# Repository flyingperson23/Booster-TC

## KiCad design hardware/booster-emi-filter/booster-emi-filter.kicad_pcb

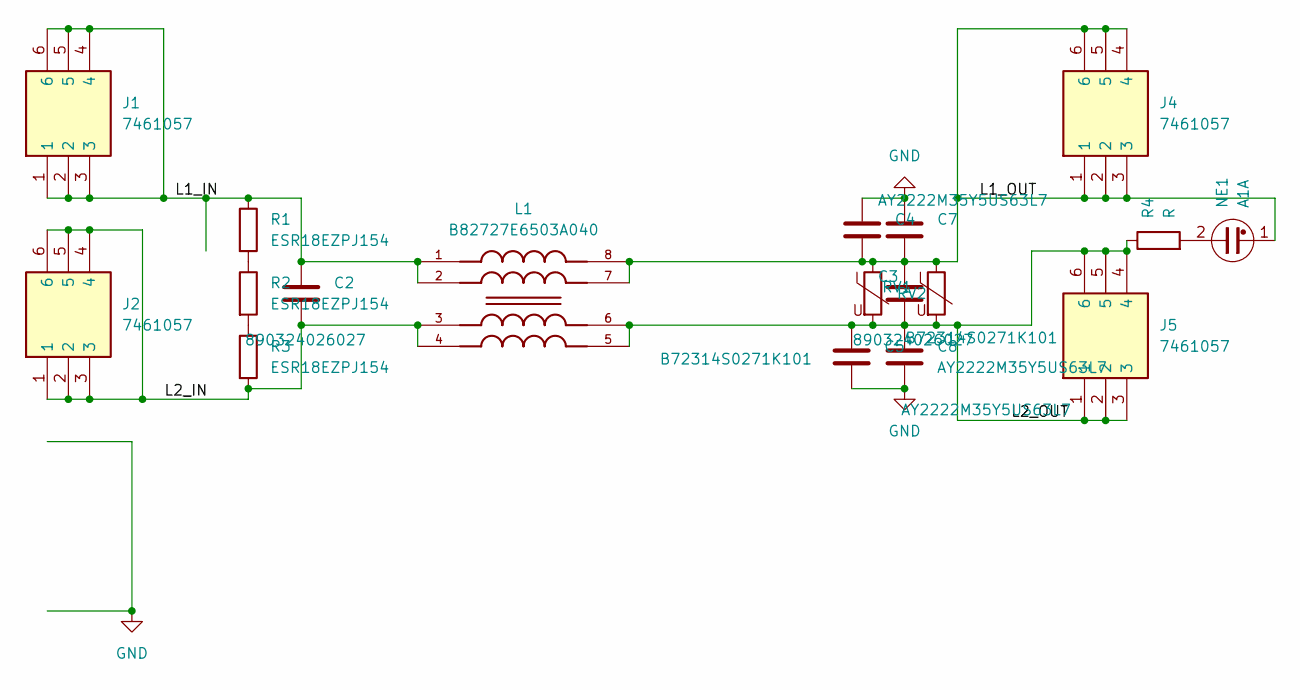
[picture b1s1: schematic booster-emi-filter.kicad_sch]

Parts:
C2, C3: 890324026027
C4, C5, C7, C8: AY2222M35Y5US63L7
J1, J2, J4, J5: 7461057; Mouser Part Number 710-7461057
L1: B82727E6503A040; IND_B82727E6503A040; PARTREV May 2015
NE1: A1A; NEON-A1A
R1, R2, R3: ESR18EZPJ154; R_1206_3216Metric_Pad1.30x1.75mm_HandSolder
R4: R; R_Axial_DIN0207_L6.3mm_D2.5mm_P7.62mm_Horizontal
RV1, RV2: B72314S0271K101

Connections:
/L1_IN: C2.1, J1.1, J1.2, J1.3, J1.4, J1.5, J1.6, L1.1, L1.2, R1.1
/L1_OUT: C3.1, C4.2, C7.2, J4.1, J4.2, J4.3, J4.4, J4.5, J4.6, L1.7, L1.8, NE1.1, RV1.1, RV2.1
/L2_IN: C2.2, J2.1, J2.2, J2.3, J2.4, J2.5, J2.6, L1.3, L1.4, R3.2
/L2_OUT: C3.2, C5.1, C8.1, J5.1, J5.2, J5.3, J5.4, J5.5, J5.6, L1.5, L1.6, R4.1, RV1.2, RV2.2
GND: C4.1, C5.2, C7.1, C8.2
unnamed: NE1.2, R4.2
unnamed: R1.2, R2.1
unnamed: R2.2, R3.1

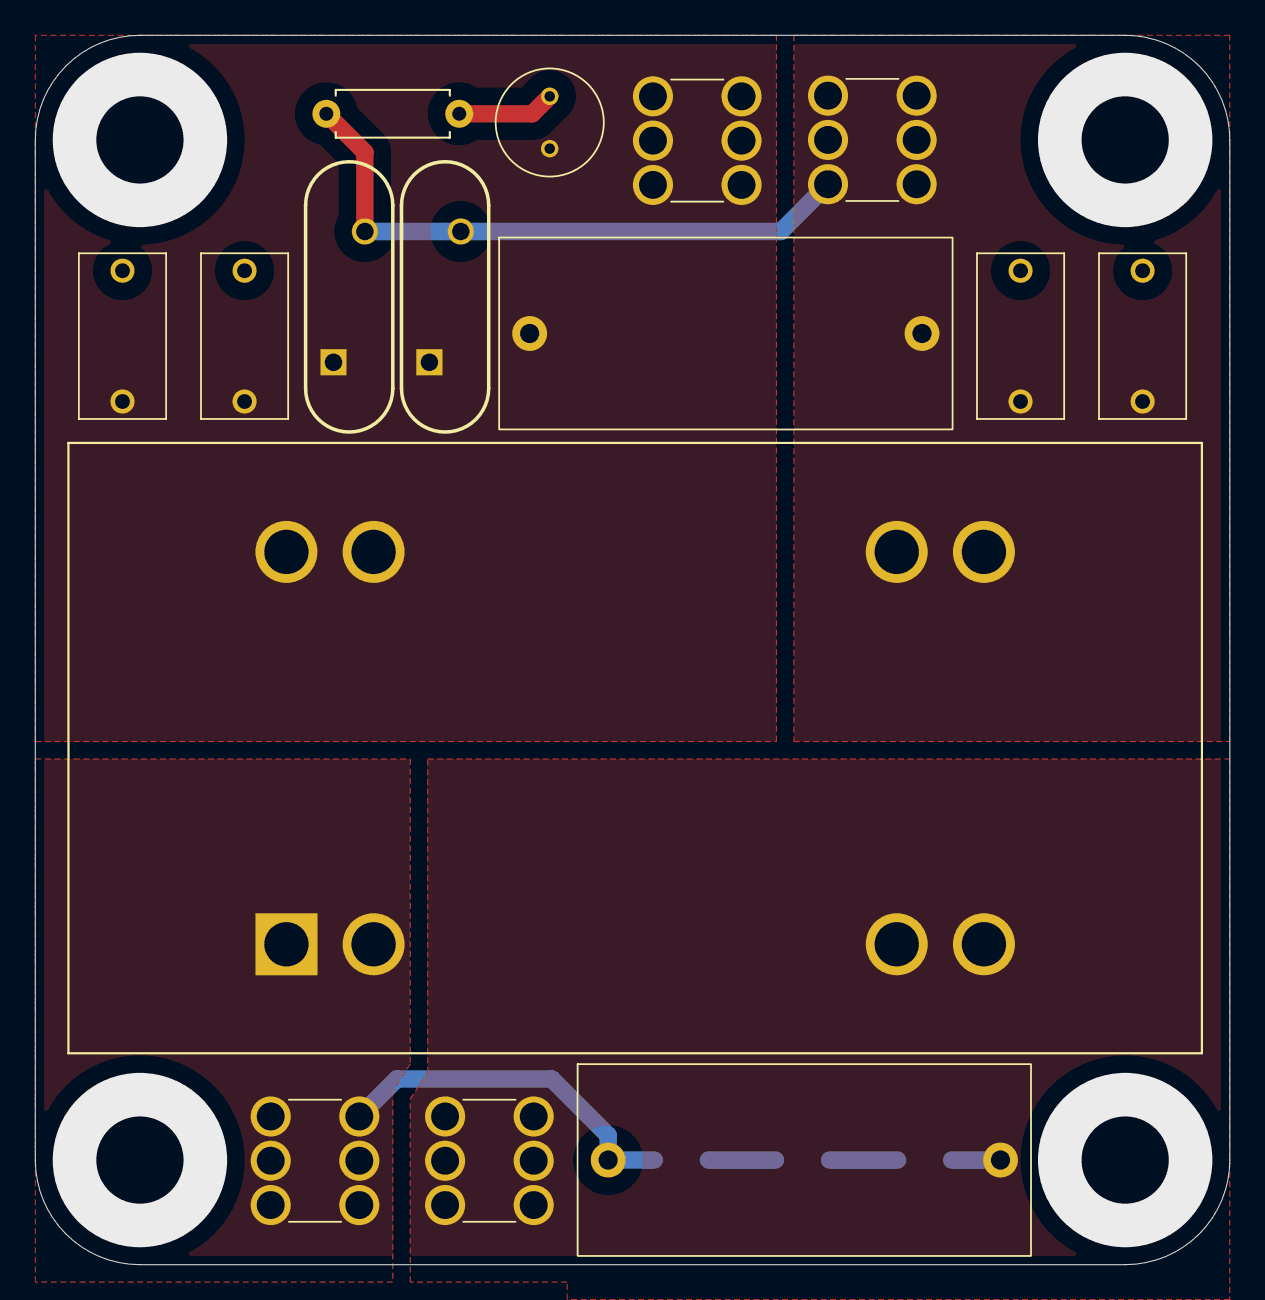
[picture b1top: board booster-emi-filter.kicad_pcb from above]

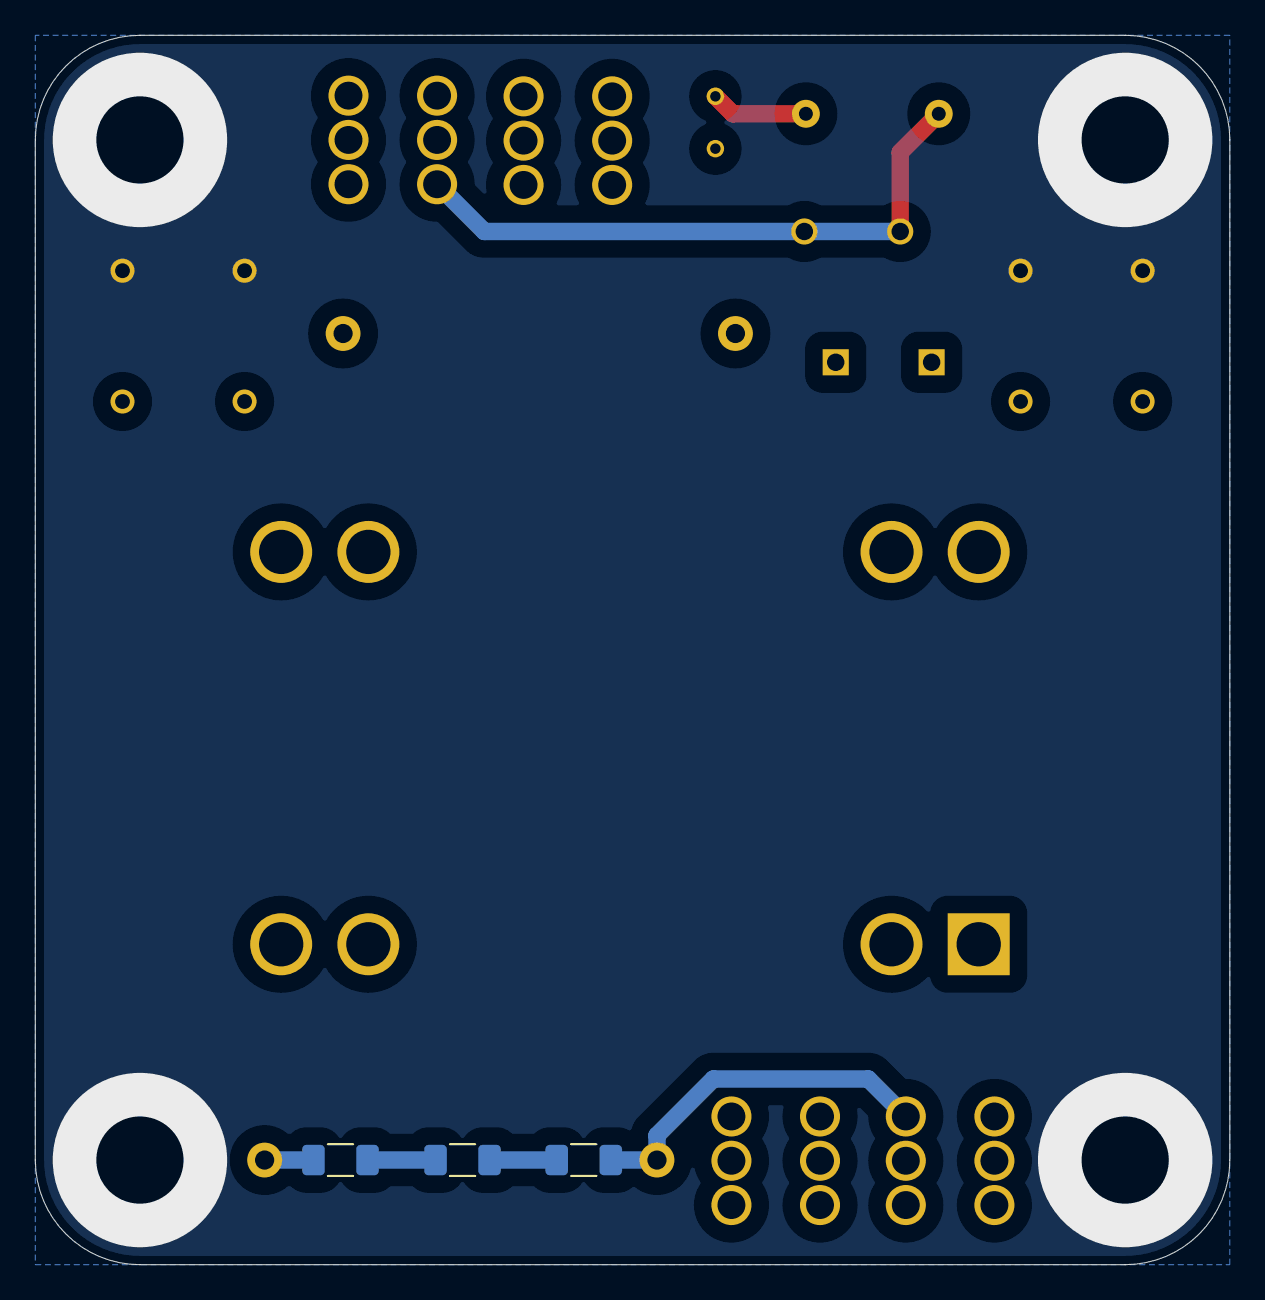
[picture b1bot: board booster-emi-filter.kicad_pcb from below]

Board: 2 copper layers, 68.5 x 70.5 mm, 18 parts (3 on the bottom side), 8 nets.

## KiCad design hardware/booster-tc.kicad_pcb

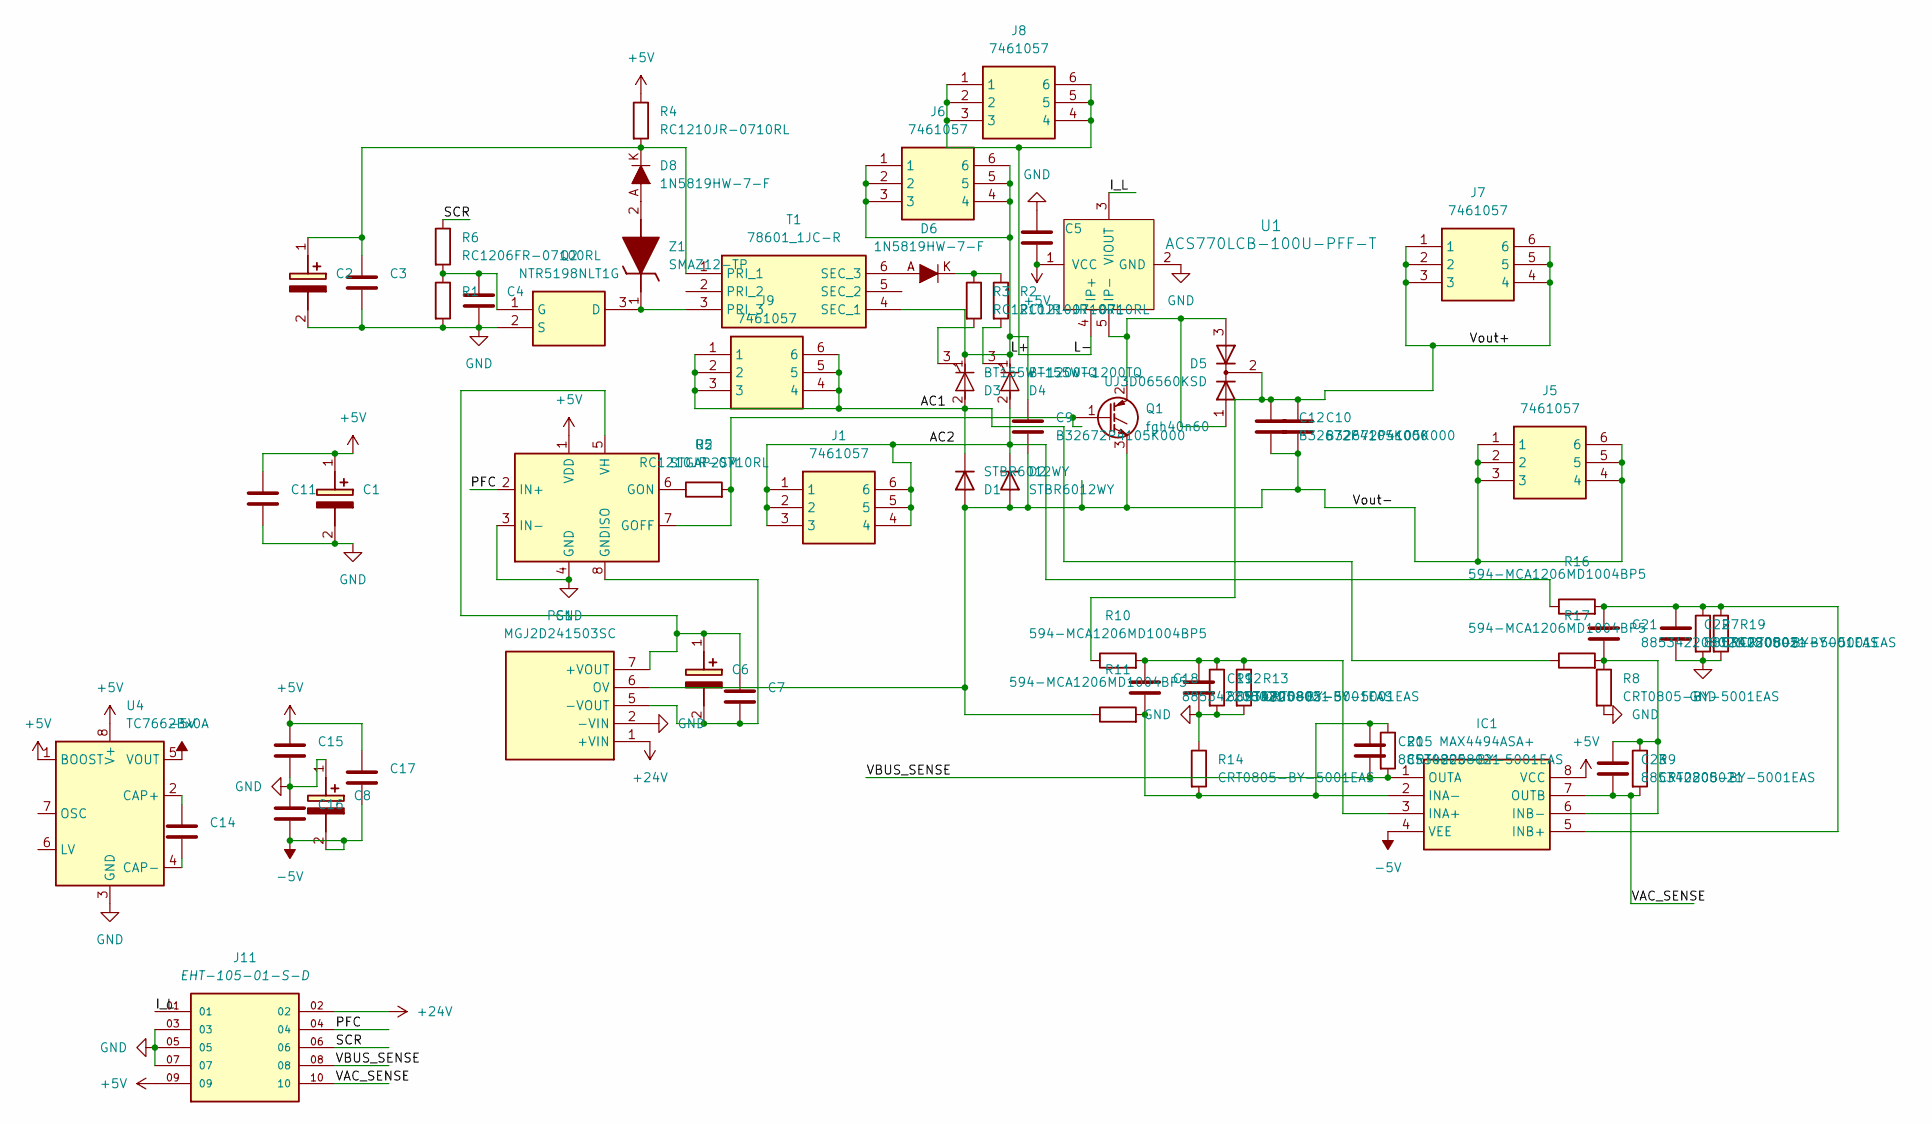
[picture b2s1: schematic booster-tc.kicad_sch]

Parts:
C1, C2, C6, C8: 860020474014; CAPPRD350W52D800H1300; Mouser Part Number 710-860020474014
C3, C5, C7: 885012210031; C_1812_4532Metric_Pad1.57x3.40mm_HandSolder
C4, C11, C14, C15, C16, C17: 885012208022; C_1206_3216Metric_Pad1.33x1.80mm_HandSolder
C9, C10, C12: B32672P4105K000
C18, C19, C20, C21, C22, C23: 885342208021; C_1206_3216Metric_Pad1.33x1.80mm_HandSolder
D1, D2: STBR6012WY; TO-247-2_Horizontal_TabDown
D3, D4: BT155W-1200TQ; TO-247-3_Horizontal_TabDown
D5: UJ3D06560KSD; TO-247-3_Horizontal_TabDown
D6, D8: 1N5819HW-7-F; SOD-123; MPN 1N5819HW-7-F
IC1: MAX4494ASA+; SOIC127P600X175-8N; Mouser Part Number 700-MAX4494ASA
J1, J5, J6, J7, J8, J9: 7461057; Mouser Part Number 710-7461057
J11: EHT-105-01-S-D; SAMTEC_EHT-105-01-S-D
PS1: MGJ2D241503SC; Mouser Part Number 580-MGJ2D241503SC
Q1: fgh40n60; TO-247-3_Horizontal_TabDown
Q2: NTR5198NLT1G; SOT96P237X111-3N; Mouser Part Number 863-NTR5198NLT1G
R1: RC1206FR-0710KL; R_1206_3216Metric
R2, R3, R4, R5: RC1210JR-0710RL; C_1210_3225Metric_Pad1.33x2.70mm_HandSolder
R6: RC1206FR-07100RL; R_1206_3216Metric_Pad1.30x1.75mm_HandSolder
R7, R8, R9, R12, R13, R14, R15, R19: CRT0805-BY-5001EAS; R_0805_2012Metric_Pad1.20x1.40mm_HandSolder
R10, R11, R16, R17: 594-MCA1206MD1004BP5; R_1206_3216Metric_Pad1.30x1.75mm_HandSolder
T1: 78601_1JC-R; SOP254P1270X665-6N; Mouser Part Number 580-78601/1JC-R
U1: ACS770LCB-100U-PFF-T; CB-5_Formed_Leads; MPN ACS770LCB-100U-PFF-T
U2: STGAP2SM; SOIC-8_3.9x4.9mm_P1.27mm
U4: TC7662Bx0A; SOIC-8_3.9x4.9mm_P1.27mm
Z1: SMAZ12-TP; DIOM5226X244N; Mouser Part Number 833-SMAZ12-TP

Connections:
+5V: C1.1 (+), C5.2, C11.1, C15.1, C17.1, IC1.8 (VCC), J11.09, R4.1, U1.1 (VCC), U2.1 (VDD), U4.1 (BOOST), U4.8 (V+)
+24V: J11.02, PS1.1 (+VIN)
-5V: C8.2 (-), C16.2, C17.2, IC1.4 (VEE), U4.5 (VOUT)
/AC1: D1.1 (K), D3.2 (A), J9.1, J9.2, J9.3, J9.4, J9.5, J9.6, R17.1
/AC2: D2.1 (K), D4.2 (A), J1.1, J1.2, J1.3, J1.4, J1.5, J1.6, R16.1
/I_L: J11.01, U1.3 (VIOUT)
/L+: C9.1, D3.1 (K), D4.1 (K), J6.1, J6.2, J6.3, J6.4, J6.5, J6.6, T1.4 (SEC_1)
/L-: J8.1, J8.2, J8.3, J8.4, J8.5, J8.6, U1.4 (IP+)
/PFC: J11.04, U2.2 (IN+)
/SCR: J11.06, R6.1
/VAC_SENSE: C23.2, IC1.7 (OUTB), J11.10, R9.2
/VBUS_SENSE: C20.2, IC1.1 (OUTA), J11.08, R15.2
/Vout+: C10.1, C12.1, D5.2 (K), J7.1, J7.2, J7.3, J7.4, J7.5, J7.6, R10.1
/Vout-: C9.2, C10.2, C12.2, D1.2 (A), D2.2 (A), J5.1, J5.2, J5.3, J5.4, J5.5, J5.6, PS1.6 (OV), Q1.3 (E), R11.1
GND: C1.2 (-), C2.2 (-), C3.2, C4.2, C5.1, C8.1 (+), C11.2, C15.2, C16.1, C19.2, C22.2, J11.03, J11.05, J11.07, PS1.2 (-VIN), Q2.2 (S), R1.2, R7.2, R8.2, R12.2, R13.2, R14.1, R19.2, U1.2 (GND), U2.3 (IN-), U2.4 (GND), U4.3 (GND)
unnamed: C2.1 (+), C3.1, D8.K, R4.2, T1.1 (PRI_1)
unnamed: C6.1 (+), C7.1, PS1.7 (+VOUT), U2.5 (VH)
unnamed: C6.2 (-), C7.2, PS1.5 (-VOUT), U2.8 (GNDISO)
unnamed: D3.3 (G), R3.2
unnamed: D4.3 (G), R2.2
unnamed: D6.K, R2.1, R3.1
unnamed: C18.1, C19.1, IC1.3 (INA+), R10.2, R12.1, R13.1
unnamed: C18.2, C20.1, IC1.2 (INA-), R11.2, R14.2, R15.1
unnamed: C21.1, C22.1, IC1.5 (INB+), R7.1, R16.2, R19.1
unnamed: C21.2, C23.1, IC1.6 (INB-), R8.1, R9.1, R17.2
unnamed: D5.1 (A), D5.3 (A), Q1.2 (C), U1.5 (IP-)
unnamed: Q1.1 (G), R5.2, U2.7 (GOFF)
unnamed: Q2.3 (D), T1.3 (PRI_3), Z1.1 (K)
unnamed: C4.1, Q2.1 (G), R1.1, R6.2
unnamed: D6.A, T1.6 (SEC_3)
unnamed: R5.1, U2.6 (GON)
unnamed: C14.1, U4.2 (CAP+)
unnamed: C14.2, U4.4 (CAP-)
unnamed: D8.A, Z1.2 (A)

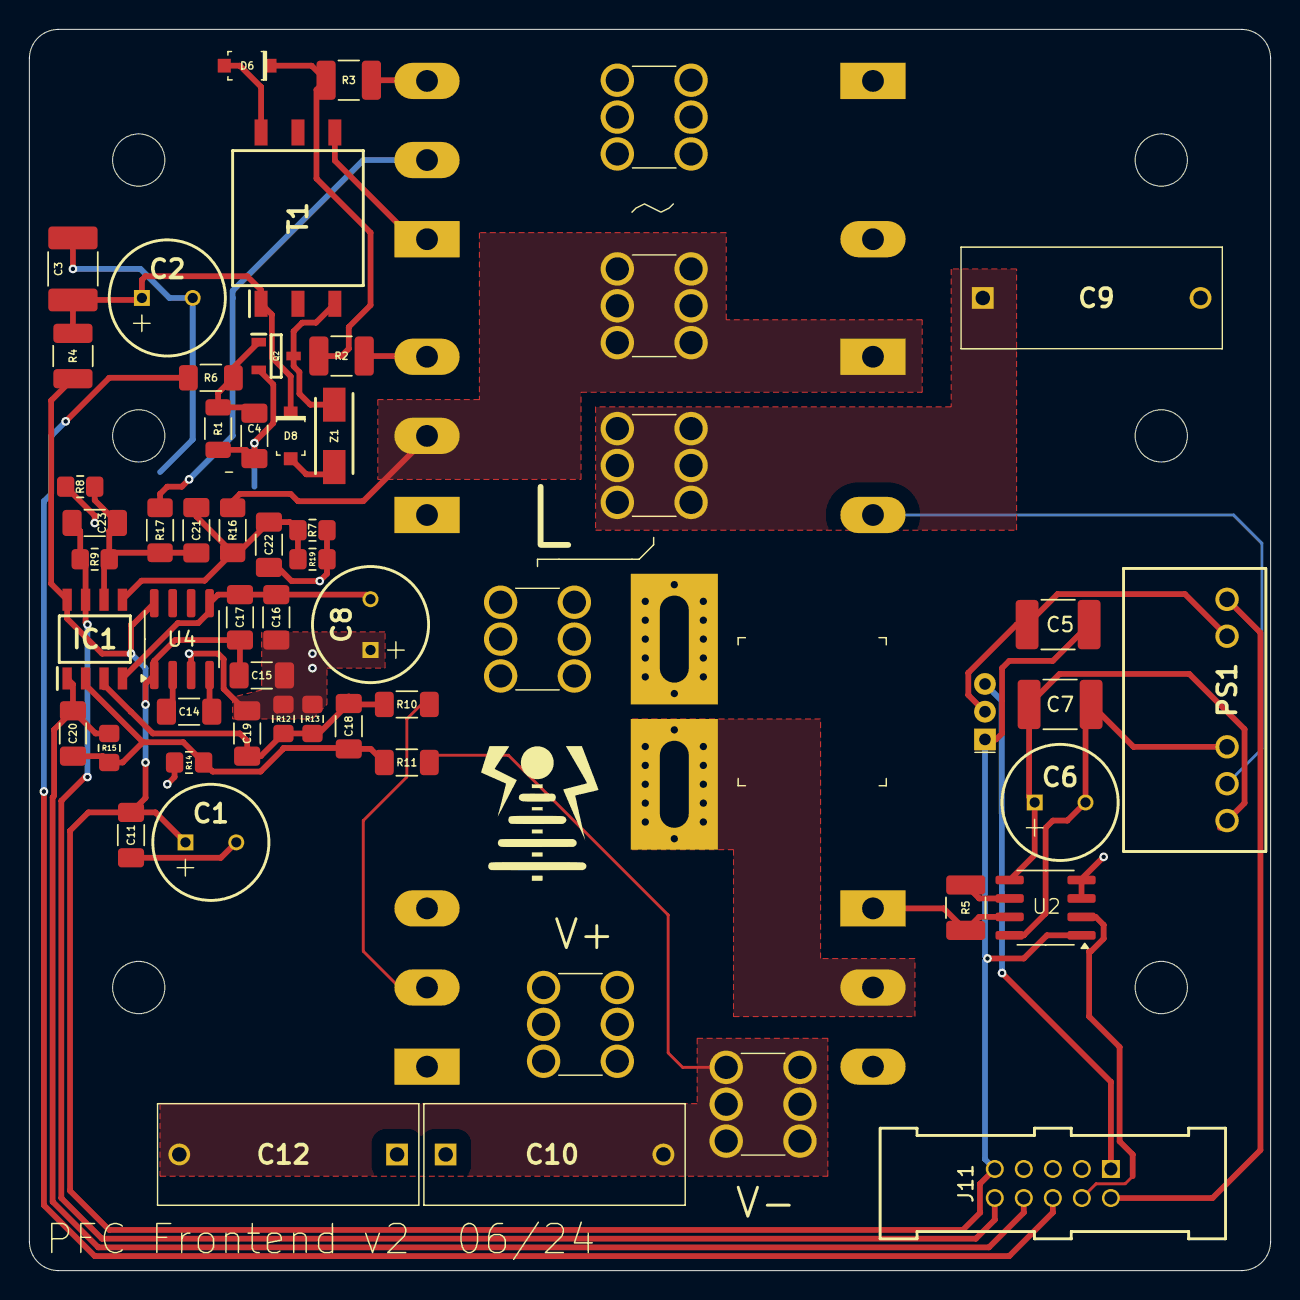
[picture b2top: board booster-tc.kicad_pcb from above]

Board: 2 copper layers, 85.5 x 85.5 mm, 63 parts (0 on the bottom side), 34 nets.
